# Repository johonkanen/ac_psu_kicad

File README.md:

# ac_psu_kicad

Migration of the **single_phase_inverter_psu_v3** board ("Inverter PSU") from Proteus 8.12
to KiCad 10. The KiCad schematic is redrawn from the Proteus PDF, and the PCB is rebuilt
from the Proteus gerbers, so that every pad, track, via and pour carries a net from the new
schematic. The goal is a KiCad design that is **electrically identical** to the Proteus
original.

The Proteus project file is binary and cannot be read, so the IPC-D-356A netlist in the
CADCAM export is the reference: 208 nets, 267 parts, 1075 pads, each with net, refdes, pin
and coordinates. Every check in this repo compares against that file.

- `PLAN.md`: the full plan, inventory of the source files, risks and model usage.
- `STATUS.md`: what is done, the last verification output, findings about the original
  design, and what comes next.
- `next_prompt.md`: the prompt for the next work session, replaced at the end of every
  phase.

## Board

<!-- board-plots:start -->
<!-- Generated by kicad-board-plots; edits between these markers are overwritten. -->

3D renders and copper layers of `kicad/ac_psu.kicad_pcb`, the layers in stack order without silkscreen. Plotted by [kicad-board-plots](https://github.com/johonkanen/kicad-board-plots) on each board change; the images live on the `renders` branch.

<table>
<tr>
<td align="center"><br><b>3D, top</b></td>
<td align="center"><br><b>3D, bottom (seen from below)</b></td>
</tr>
<tr>
<td align="center"><br><b>F.Cu: signal, FILTER_INPUT, DC+, DAB_CAP_PRI, 5V_ISOL, ISOPGND and 20 more pours (top)</b></td>
<td align="center"><br><b>In1.Cu: signal, DAB_SOURCE_HI_PRI, ISOGND, PGND, Q7_G, GND and 8 more pours</b></td>
</tr>
<tr>
<td align="center"><br><b>In2.Cu: signal, G3_SOURCE_HI, DAB_SOURCE_HI_SEC, PGND, Q7_S, DAB_GATE_HI_PRI and 8 more pours</b></td>
<td align="center"><br><b>B.Cu: signal, 15V_ISO, DAB_SOURCE_HI_SEC, SHUNT1_FORCE, ISODC+, INDUCTOR_OUTPUT and 12 more pours (bottom, seen from the top)</b></td>
</tr>
</table>

<!-- board-plots:end -->

## Layout

```
source/      Proteus exports (read-only): schematic PDF + page renders, CADCAM zip
             (gerbers, drill, IPC-D-356A netlist)
reference/   tables generated from the IPC netlist: pads (CSV/JSON), pin→net per part,
             pins per net
lib/         ac_psu.kicad_sym (project symbols, pin numbers = IPC pin ids),
             ac_psu.pretty (project footprints), part_map.csv (refdes → sheet, symbol,
             value), footprint_map.csv (refdes → footprint)
kicad/       KiCad project: root sheet + 11 hierarchical sheets, ac_psu.kicad_pcb
             (Proteus-generated up to tag proteus-conversion-complete, v4 edits by tools/v4/)
tools/       scripts and checks (see below)
reports/     generated reports: footprint fit, net assignment, pour nets (committed);
             ERC and DRC (not committed)
```

## Phases

| Phase | Content | State |
|---|---|---|
| 0 | Tooling: KiCad AppImage wrappers, IPC-D-356A parser, pin/net reference tables | done |
| 1 | Schematic: symbol library and part map, netlist comparison script, project skeleton, transcription of the 11 sheets from the PDF | done |
| 2 | Footprints for every symbol, pad numbers = IPC pin ids, checked by fitting footprint pads onto the IPC pad coordinates | done |
| 3 | PCB: place footprints at the Proteus positions, convert gerber tracks/vias/pours into KiCad tracks, vias and zones, assign nets by copper connectivity | done |
| 4 | Verification: schematic netlist ≡ IPC, DRC clean, gerber round-trip overlay, regenerated IPC-356 pad list diff | not started |

`STATUS.md` holds the current state; this table is only updated when a phase finishes.

## Requirements

- KiCad 10.0.7 AppImage at `~/kicad/kicad-10.0.7-x86_64.AppImage`. The scripts mount it
  on demand and use its `kicad-cli` and Python (with `pcbnew`). Do not run the AppImage
  with `--version`; it hangs.
- Python 3 for the plain scripts.

## Tools

The generic tools are the shared [proteus2kicad](https://github.com/johonkanen/proteus2kicad)
repository, a git submodule in `tools/p2k` (clone with `git clone --recurse-submodules`, or
run `git submodule update --init`). Board values (source files, refdes/net fix-ups, expected
counts, layers, outline) are in `p2k_config.py`. The scripts in `tools/` are the ones not
moved yet; they import the shared modules from `p2k`. Wrappers: `tools/p2k/bin/p2k <tool>`,
`tools/p2k/bin/kipy` (KiCad's Python with pcbnew), `tools/p2k/bin/kicad-cli`.
The generic migration method distilled from this board, the playbook, is in proteus2kicad
(`tools/p2k/CONVERSION_PLAYBOOK.md`).

## Checks

Run everything with one command:

```sh
tools/check_all.sh
```

It runs:

| Step | Script |
|---|---|
| KiCad environment (pcbnew 10.0.7 loads) | `tools/p2k/bin/kipy` |
| IPC parser self-check | `tools/p2k/bin/p2k ipc356 --check` |
| Gerber X2 flashes and drills vs IPC, outline | `tools/p2k/bin/p2k check_sources` |
| Symbol library is up to date with its generator | `tools/gen_symbols.py --check` |
| Symbol pin sets match the IPC pins for every refdes (+ v4 deviations) | `tools/check_symbols_v4.py` |
| ERC | `tools/erc.sh` (report in `reports/erc.rpt`) |
| Schematic netlist vs IPC netlist (+ v4 deviations, values) | `tools/compare_netlists_v4.py` |
| Footprint library and map are up to date | `tools/gen_footprints.py --check` |
| Footprint pads fit the IPC pads (≤ 0.05 mm) | `tools/check_footprints.py --pcbnew` |
| Board pads/holes/vias vs IPC (position and net) | `tools/check_board.py` |
| Copper connectivity after zone fill: 0 shorts, 0 opens, every item on its group's net | `tools/assign_nets.py --check` |
| DRC with schematic parity: 0 shorts, 0 unconnected | `tools/drc.py` (report in `reports/drc.json`) |
| Domain net classes / DRC rules match the schematic (IEC 61010-1 gaps P, I, C, E) | `tools/v4/domain_rules.py --check` |
| Insulation spacing between the domains on every layer | `tools/v4/domain_gaps.py` |
| IPC-D-356 export vs Proteus, gerber round trip | `tools/ipc356_diff.py`, `tools/gerber_roundtrip.py --check` |

`p2k compare_netlists` exports the KiCad netlist and compares nets as sets of
(refdes, pin), so net names do not have to match. It reports pins on the wrong net, merged
or split nets, N/C mismatches, missing or extra parts and pins, and progress per sheet.
Use `--sheet N` to check one sheet while drawing.

Other tools: `gen_symbols.py` builds `lib/ac_psu.kicad_sym` from KiCad standard symbols
and box symbols (helpers in `p2k.symgen`); `p2k.sch_builder` is a small library for writing schematic sheets from
Python; `p2k.sexpr` reads and writes KiCad s-expression files; `p2k make_skeleton` created
the project skeleton once; `tools/sheets/sheetNN.py` generate the 11 sheets.

**v5** (aux flyback, control-card isolation; V5_PLAN.md, CTRL_ISOLATION_PLAN.md): parts in
`tools/v5/v5_parts.py`, deviations in `lib/v5_deviations.csv` / `lib/v5_copper.csv` (kinds remove,
rename, and pending-layout areas where the checks list items as pending), board step
`tools/v5/v5_1_aux_ctrl.py`; the layout itself is done in the KiCad GUI.

**Since v4 the design board `kicad/ac_psu.kicad_pcb` is frozen**: it is edited directly by small
committed pcbnew scripts (`tools/v4/fix_*.py`, see STATUS.md "v4 design fixes"), and the Proteus
comparisons apply exactly the deviations listed in `lib/v4_deviations.csv` / `lib/v4_copper.csv`
(`tools/deviations.py`; wrappers `tools/compare_netlists_v4.py`, `tools/check_symbols_v4.py`).
`tools/make_pcb.sh` now rebuilds the *Proteus* board from the schematic at tag
`proteus-conversion-complete` into `build/proteus/` (regression check of the conversion tools,
`tools/regen_check.sh`). The Proteus board was built with `tools/make_pcb.sh`: `build_pcb.py` (footprints, nets, outline,
mounting holes), `gerber_to_tracks.py` (Proteus copper gerbers → tracks and vias, using
`p2k.gerber`), `assign_nets.py` (nets by copper connectivity, `p2k.geom2d`) and
`pours_to_zones.py` (Proteus pours → filled zones). The output is reproducible byte for byte.

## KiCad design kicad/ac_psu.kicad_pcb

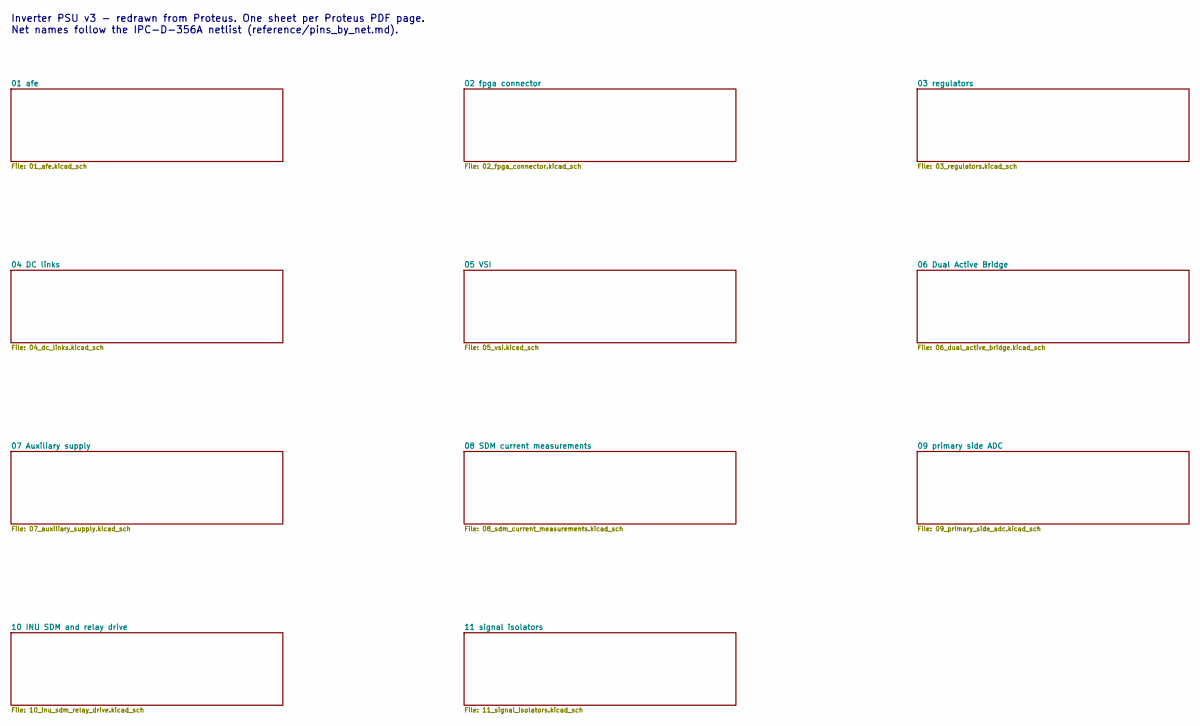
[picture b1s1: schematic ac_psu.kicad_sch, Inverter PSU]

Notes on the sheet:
Inverter PSU v3 - redrawn from Proteus. One sheet per Proteus PDF page. Net names follow the IPC-D-356A netlist (reference/pins_by_net.md).

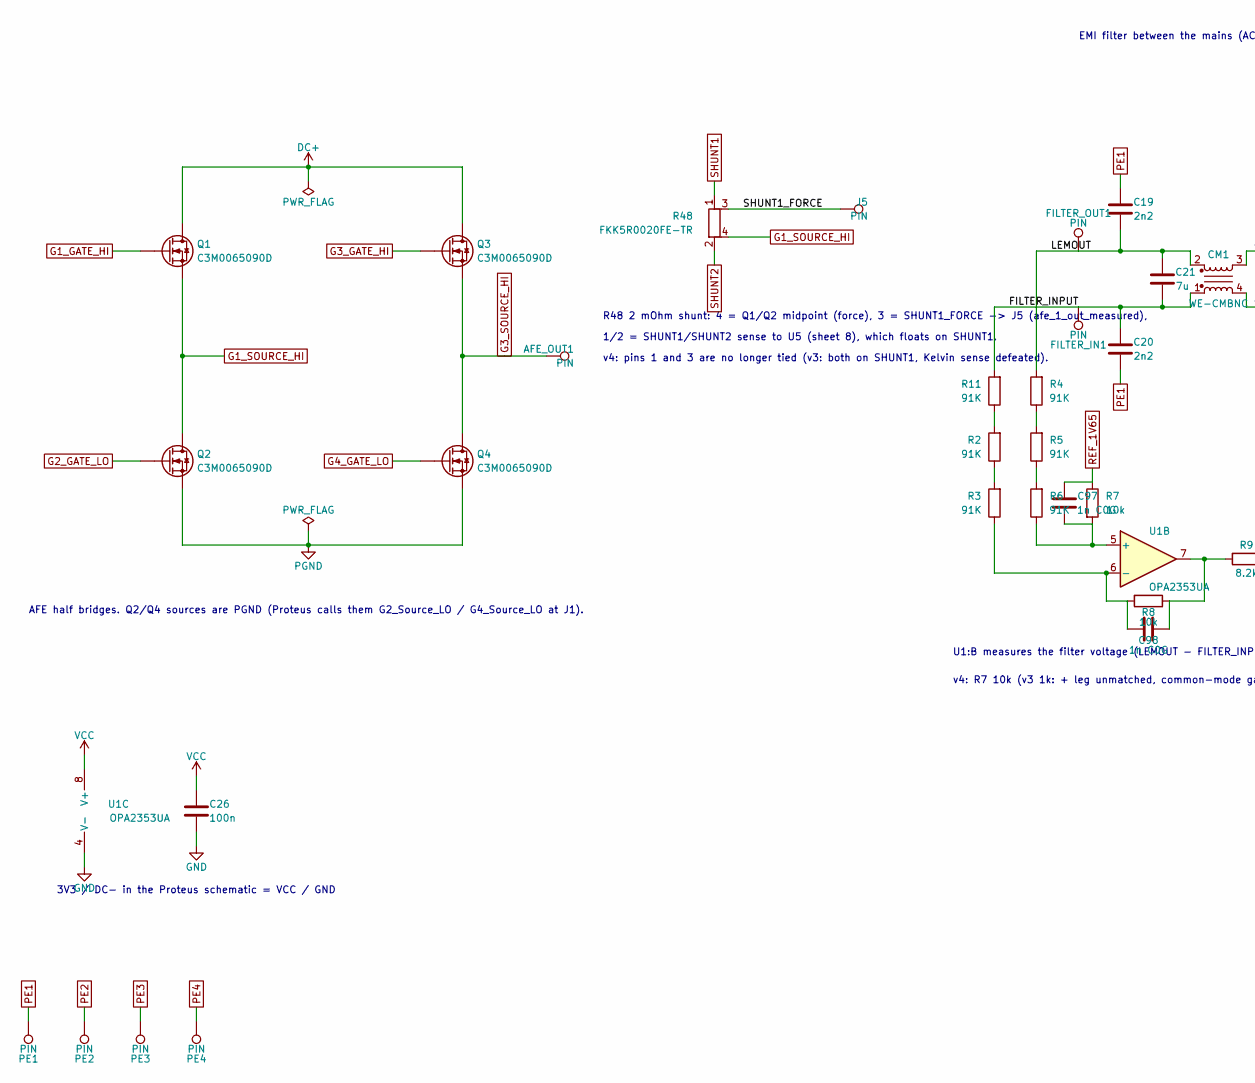
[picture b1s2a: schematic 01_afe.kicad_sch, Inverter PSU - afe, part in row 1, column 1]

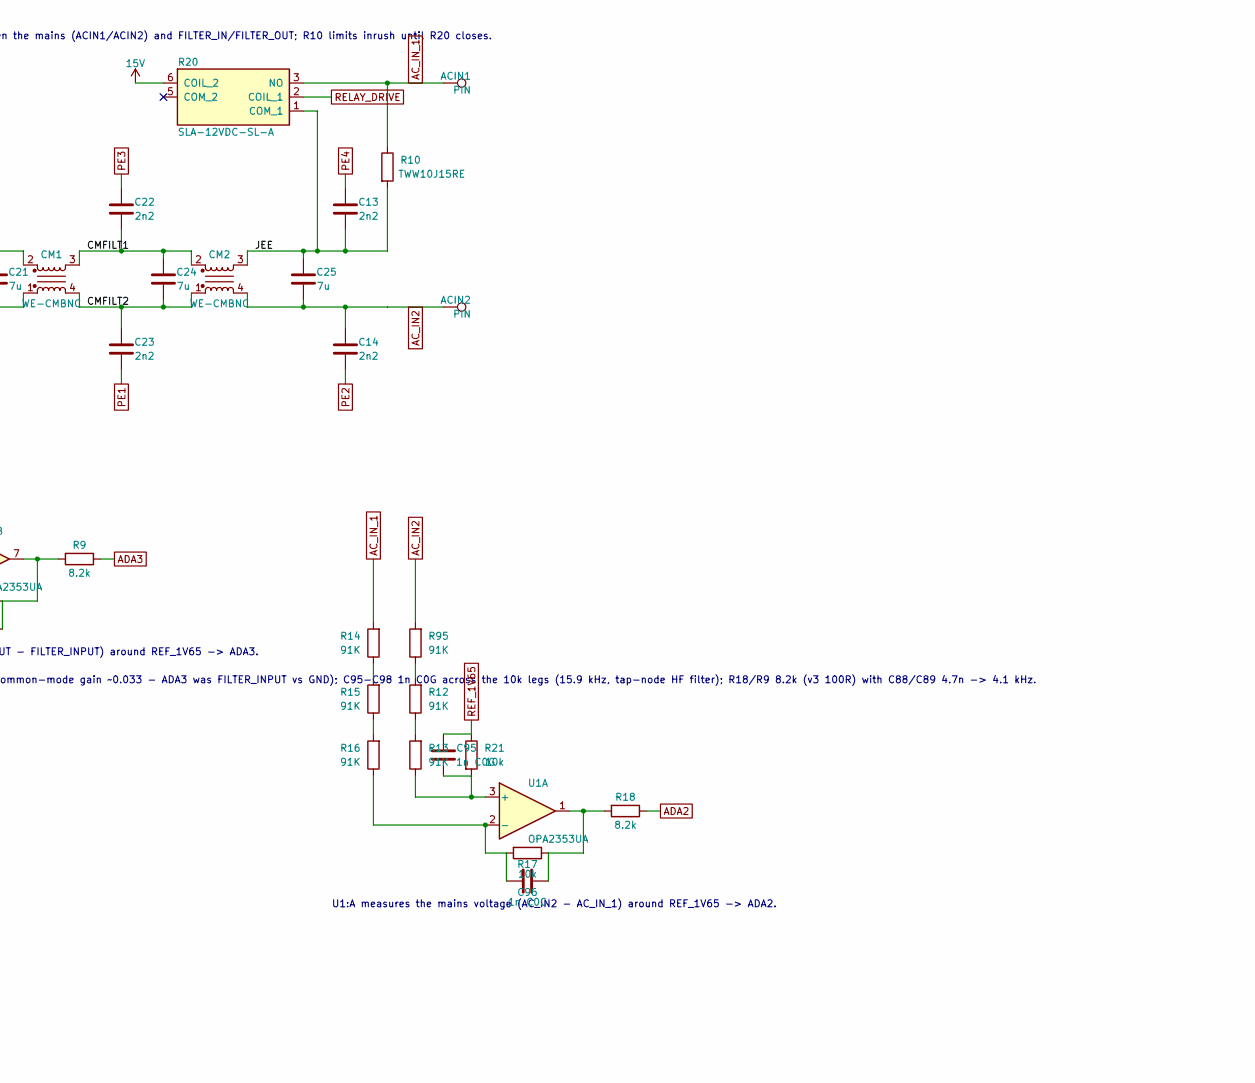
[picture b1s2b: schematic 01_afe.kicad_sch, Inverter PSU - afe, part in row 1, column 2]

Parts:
ACIN1, ACIN2: PIN; Terminal_2x1_P5.00mm_D2.0mm_Drill1.4mm
AFE_OUT1: PIN; Terminal_D4.0mm_Drill2.55mm
C13, C14, C19, C20, C22, C23: 2n2; C_Disc_D12.5mm_W5.0mm_P7.50mm
C21, C25: 7u; C_Rect_L33.0mm_W20.0mm_P27.50mm_MKS4_Proteus
C24: 7u; C_Rect_L33.0mm_W20.0mm_P27.50mm_MKS4
C26: 100n; C_0402_1005Metric
C95, C96, C97, C98: 1n C0G; C_0402_1005Metric
CM1, CM2: WE-CMBNC; L_CommonMode_WE-CMBNC
FILTER_IN1: PIN; Wuerth_REDCUBE-THR_74650074_M4_PTH
FILTER_OUT1: PIN; Wuerth_REDCUBE-THR_74650074_M4_PTH
J5: PIN; Wuerth_REDCUBE-THR_74650074_M4_PTH
PE1: PIN; Terminal_D4.0mm_Drill3.0mm
PE2, PE4: PIN; Terminal_D4.0mm_Drill2.0mm
PE3: PIN; Terminal_D4.0mm_Drill2.55mm
Q1, Q2, Q3, Q4: C3M0065090D; TO-247-3_Vertical_Proteus
R2, R3, R4, R5, R6, R11, R12, R13, R14, R15, R16, R95: 91K; R_1206_3216Metric_Pad1.30x1.75mm_HandSolder
R7, R8, R17, R21: 10k; R_0402_1005Metric
R9, R18: 8.2k; R_0402_1005Metric
R10: TWW10J15RE; R_Radial_Power_L13.0mm_W9.0mm_P5.00mm
R20: SLA-12VDC-SL-A; Relay_SLA-12VDC-SL-A
R48: FKK5R0020FE-TR; R_Shunt_FKK5R0020FE
U1: OPA2353UA; TSSOP-8_3x3mm_P0.65mm_Proteus

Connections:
15V: R20.6 (COIL_2); also elsewhere on the board
/01 afe/CMFILT1: C22.2, C24.1, CM1.3, CM2.2
/01 afe/CMFILT2: C23.2, C24.2, CM1.4, CM2.1
/01 afe/FILTER_INPUT: C20.2, C21.2, CM1.1, FILTER_IN1.1, R11.2
/01 afe/JEE: C13.2, C25.1, CM2.3, R10.2, R20.1 (COM_1)
/01 afe/LEMOUT: C19.2, C21.1, CM1.2, FILTER_OUT1.1, R4.2
/01 afe/SHUNT1_FORCE: J5.1, R48.3
AC_IN2: ACIN2.1, C14.2, C25.2, CM2.4, R95.2
AC_IN_1: ACIN1.1, R10.1, R14.2, R20.3 (NO)
ADA2: R18.1; also elsewhere on the board
ADA3: R9.1; also elsewhere on the board
DC+: Q1.2 (D), Q3.2 (D); also elsewhere on the board
G1_GATE_HI: Q1.1 (G); also elsewhere on the board
G1_SOURCE_HI: Q1.3 (S), Q2.2 (D), R48.4; also elsewhere on the board
G2_GATE_LO: Q2.1 (G); also elsewhere on the board
G3_GATE_HI: Q3.1 (G); also elsewhere on the board
G3_SOURCE_HI: AFE_OUT1.1, Q3.3 (S), Q4.2 (D); also elsewhere on the board
G4_GATE_LO: Q4.1 (G); also elsewhere on the board
GND: C26.1, U1.4 (V-); also elsewhere on the board
unnamed: C96.1, R17.1, R18.2, U1.1
unnamed: C98.1, R8.1, R9.2, U1.7
unnamed: R2.1, R3.2
unnamed: R4.1, R5.2
unnamed: R5.1, R6.2
unnamed: R2.2, R11.1
unnamed: R12.1, R13.2
unnamed: R12.2, R95.1
unnamed: R14.1, R15.2
unnamed: R15.1, R16.2
unnamed: C95.2, R13.1, R21.2, U1.3 (+)
unnamed: C96.2, R16.1, R17.2, U1.2 (-)
unnamed: C97.2, R6.1, R7.2, U1.5 (+)
unnamed: C98.2, R3.1, R8.2, U1.6 (-)
PE1: C19.1, C20.1, C23.1, PE1.1
PE2: C14.1, PE2.1
PE3: C22.1, PE3.1
PE4: C13.1, PE4.1
PGND: Q2.3 (S), Q4.3 (S); also elsewhere on the board
REF_1V65: C95.1, C97.1, R7.1, R21.1; also elsewhere on the board
RELAY_DRIVE: R20.2 (COIL_1); also elsewhere on the board
SHUNT1: R48.1; also elsewhere on the board
SHUNT2: R48.2; also elsewhere on the board
VCC: C26.2, U1.8 (V+); also elsewhere on the board

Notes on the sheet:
AFE half bridges. Q2/Q4 sources are PGND (Proteus calls them G2_Source_LO / G4_Source_LO at J1).
R48 2 mOhm shunt: 4 = Q1/Q2 midpoint (force), 3 = SHUNT1_FORCE -> J5 (afe_1_out_measured),
1/2 = SHUNT1/SHUNT2 sense to U5 (sheet 8), which floats on SHUNT1.
v4: pins 1 and 3 are no longer tied (v3: both on SHUNT1, Kelvin sense defeated).
EMI filter between the mains (ACIN1/ACIN2) and FILTER_IN/FILTER_OUT; R10 limits inrush until R20 closes.
U1:B measures the filter voltage (LEMOUT - FILTER_INPUT) around REF_1V65 -> ADA3.
v4: R7 10k (v3 1k: + leg unmatched, common-mode gain ~0.033 - ADA3 was FILTER_INPUT vs GND); C95-C98 1n C0G across the 10k legs (15.9 kHz, tap-node HF filter); R18/R9 8.2k (v3 100R) with C88/C89 4.7n -> 4.1 kHz.
U1:A measures the mains voltage (AC_IN2 - AC_IN_1) around REF_1V65 -> ADA2.
3V3 / DC- in the Proteus schematic = VCC / GND

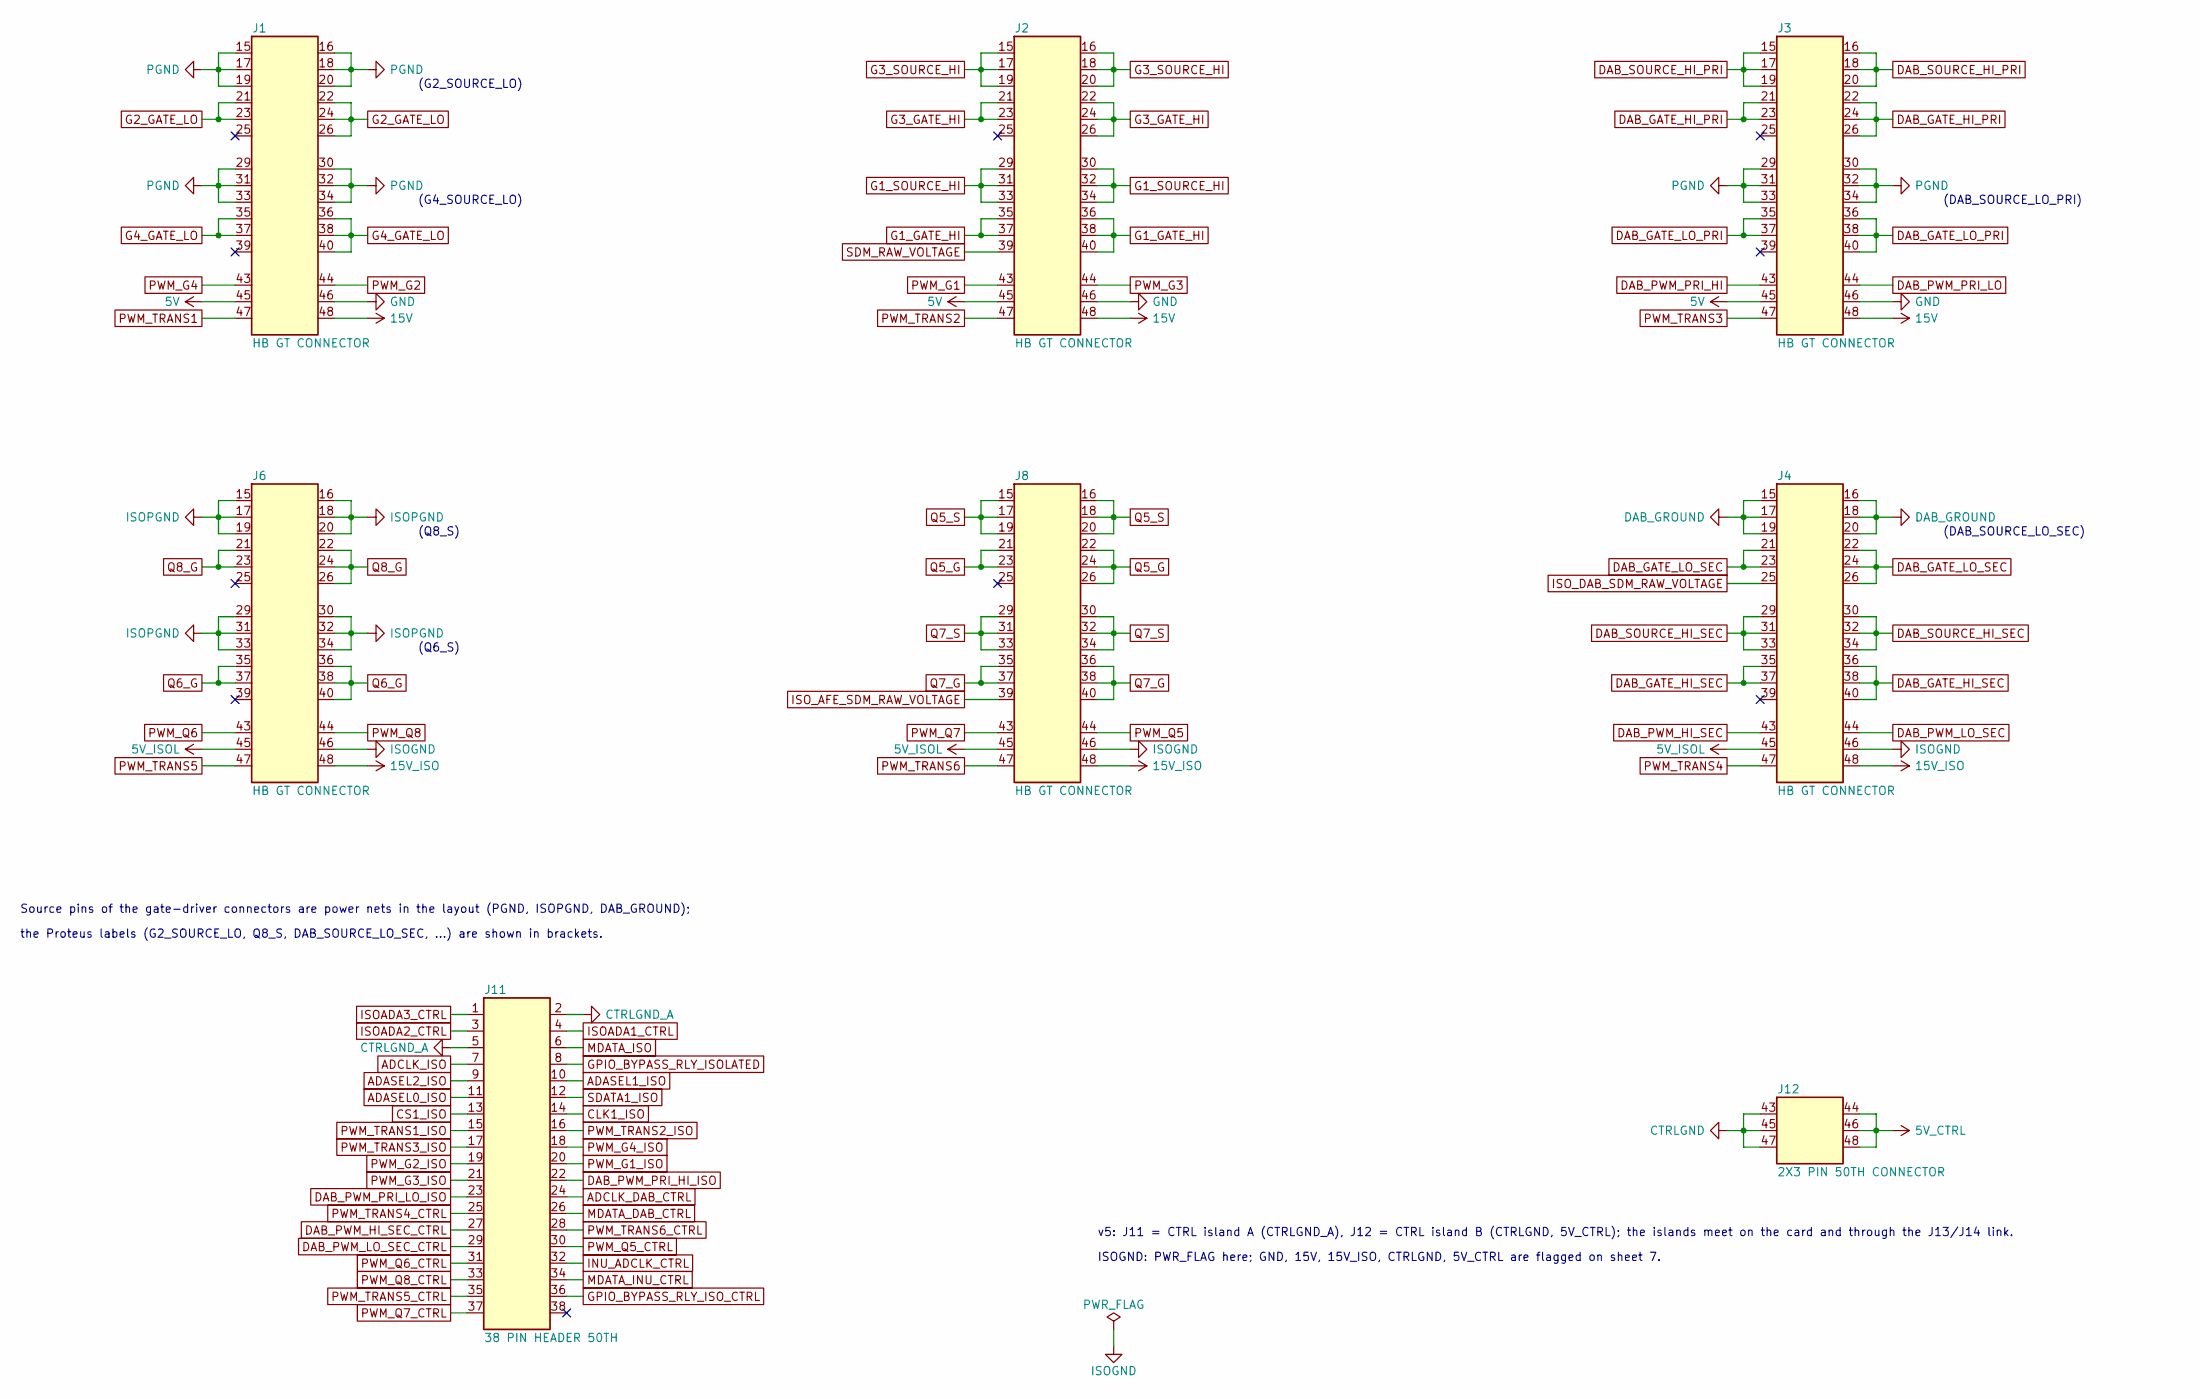
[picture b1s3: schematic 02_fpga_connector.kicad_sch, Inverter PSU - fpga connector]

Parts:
J1, J2, J3, J4, J6, J8: HB GT CONNECTOR; PinHeader_2x24_P1.27mm_Vertical_Pins15-48
J11: 38 PIN HEADER 50TH; PinHeader_2x19_P1.27mm_Vertical_Proteus
J12: 2X3 PIN 50TH CONNECTOR; PinHeader_2x03_P1.27mm_Vertical_Pins43-48

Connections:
5V: J1.45, J2.45, J3.45; also elsewhere on the board
5V_CTRL: J12.44, J12.46, J12.48; also elsewhere on the board
5V_ISOL: J4.45, J6.45, J8.45; also elsewhere on the board
15V: J1.48, J2.48, J3.48; also elsewhere on the board
15V_ISO: J4.48, J6.48, J8.48; also elsewhere on the board
ADASEL0_ISO: J11.11; also elsewhere on the board
ADASEL1_ISO: J11.10; also elsewhere on the board
ADASEL2_ISO: J11.9; also elsewhere on the board
ADCLK_DAB_CTRL: J11.24; also elsewhere on the board
ADCLK_ISO: J11.7; also elsewhere on the board
CLK1_ISO: J11.14; also elsewhere on the board
CS1_ISO: J11.13; also elsewhere on the board
CTRLGND: J12.43, J12.45, J12.47; also elsewhere on the board
CTRLGND_A: J11.2, J11.5; also elsewhere on the board
DAB_GATE_HI_PRI: J3.21, J3.22, J3.23, J3.24, J3.26; also elsewhere on the board
DAB_GATE_HI_SEC: J4.35, J4.36, J4.37, J4.38, J4.40; also elsewhere on the board
DAB_GATE_LO_PRI: J3.35, J3.36, J3.37, J3.38, J3.40; also elsewhere on the board
DAB_GATE_LO_SEC: J4.21, J4.22, J4.23, J4.24, J4.26; also elsewhere on the board
DAB_GROUND: J4.15, J4.16, J4.17, J4.18, J4.19, J4.20; also elsewhere on the board
DAB_PWM_HI_SEC: J4.43; also elsewhere on the board
DAB_PWM_HI_SEC_CTRL: J11.27; also elsewhere on the board
DAB_PWM_LO_SEC: J4.44; also elsewhere on the board
DAB_PWM_LO_SEC_CTRL: J11.29; also elsewhere on the board
DAB_PWM_PRI_HI: J3.43; also elsewhere on the board
DAB_PWM_PRI_HI_ISO: J11.22; also elsewhere on the board
DAB_PWM_PRI_LO: J3.44; also elsewhere on the board
DAB_PWM_PRI_LO_ISO: J11.23; also elsewhere on the board
DAB_SOURCE_HI_PRI: J3.15, J3.16, J3.17, J3.18, J3.19, J3.20; also elsewhere on the board
DAB_SOURCE_HI_SEC: J4.29, J4.30, J4.31, J4.32, J4.33, J4.34; also elsewhere on the board
G1_GATE_HI: J2.35, J2.36, J2.37, J2.38, J2.40; also elsewhere on the board
G1_SOURCE_HI: J2.29, J2.30, J2.31, J2.32, J2.33, J2.34; also elsewhere on the board
G2_GATE_LO: J1.21, J1.22, J1.23, J1.24, J1.26; also elsewhere on the board
G3_GATE_HI: J2.21, J2.22, J2.23, J2.24, J2.26; also elsewhere on the board
G3_SOURCE_HI: J2.15, J2.16, J2.17, J2.18, J2.19, J2.20; also elsewhere on the board
G4_GATE_LO: J1.35, J1.36, J1.37, J1.38, J1.40; also elsewhere on the board
GND: J1.46, J2.46, J3.46; also elsewhere on the board
GPIO_BYPASS_RLY_ISOLATED: J11.8; also elsewhere on the board
GPIO_BYPASS_RLY_ISO_CTRL: J11.36; also elsewhere on the board
INU_ADCLK_CTRL: J11.32; also elsewhere on the board
ISOADA1_CTRL: J11.4; also elsewhere on the board
ISOADA2_CTRL: J11.3; also elsewhere on the board
ISOADA3_CTRL: J11.1; also elsewhere on the board
ISOGND: J4.46, J6.46, J8.46; also elsewhere on the board
ISOPGND: J6.15, J6.16, J6.17, J6.18, J6.19, J6.20, J6.29, J6.30, J6.31, J6.32, J6.33, J6.34; also elsewhere on the board
ISO_AFE_SDM_RAW_VOLTAGE: J8.39; also elsewhere on the board
ISO_DAB_SDM_RAW_VOLTAGE: J4.25; also elsewhere on the board
MDATA_DAB_CTRL: J11.26; also elsewhere on the board
MDATA_INU_CTRL: J11.34; also elsewhere on the board
MDATA_ISO: J11.6; also elsewhere on the board
PGND: J1.15, J1.16, J1.17, J1.18, J1.19, J1.20, J1.29, J1.30, J1.31, J1.32, J1.33, J1.34, J3.29, J3.30, J3.31, J3.32, J3.33, J3.34; also elsewhere on the board
PWM_G1: J2.43; also elsewhere on the board
PWM_G1_ISO: J11.20; also elsewhere on the board
PWM_G2: J1.44; also elsewhere on the board
PWM_G2_ISO: J11.19; also elsewhere on the board
PWM_G3: J2.44; also elsewhere on the board
PWM_G3_ISO: J11.21; also elsewhere on the board
PWM_G4: J1.43; also elsewhere on the board
PWM_G4_ISO: J11.18; also elsewhere on the board
PWM_Q5: J8.44; also elsewhere on the board
PWM_Q5_CTRL: J11.30; also elsewhere on the board
PWM_Q6: J6.43; also elsewhere on the board
PWM_Q6_CTRL: J11.31; also elsewhere on the board
PWM_Q7: J8.43; also elsewhere on the board
PWM_Q7_CTRL: J11.37; also elsewhere on the board
PWM_Q8: J6.44; also elsewhere on the board
PWM_Q8_CTRL: J11.33; also elsewhere on the board
PWM_TRANS1: J1.47; also elsewhere on the board
PWM_TRANS1_ISO: J11.15; also elsewhere on the board
PWM_TRANS2: J2.47; also elsewhere on the board
PWM_TRANS2_ISO: J11.16; also elsewhere on the board
PWM_TRANS3: J3.47; also elsewhere on the board
PWM_TRANS3_ISO: J11.17; also elsewhere on the board
PWM_TRANS4: J4.47; also elsewhere on the board
PWM_TRANS4_CTRL: J11.25; also elsewhere on the board
PWM_TRANS5: J6.47; also elsewhere on the board
PWM_TRANS5_CTRL: J11.35; also elsewhere on the board
PWM_TRANS6: J8.47; also elsewhere on the board
PWM_TRANS6_CTRL: J11.28; also elsewhere on the board
Q5_G: J8.21, J8.22, J8.23, J8.24, J8.26; also elsewhere on the board
Q5_S: J8.15, J8.16, J8.17, J8.18, J8.19, J8.20; also elsewhere on the board
Q6_G: J6.35, J6.36, J6.37, J6.38, J6.40; also elsewhere on the board
Q7_G: J8.35, J8.36, J8.37, J8.38, J8.40; also elsewhere on the board
Q7_S: J8.29, J8.30, J8.31, J8.32, J8.33, J8.34; also elsewhere on the board
Q8_G: J6.21, J6.22, J6.23, J6.24, J6.26; also elsewhere on the board
SDATA1_ISO: J11.12; also elsewhere on the board
SDM_RAW_VOLTAGE: J2.39; also elsewhere on the board

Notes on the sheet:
(G2_SOURCE_LO)
(G4_SOURCE_LO)
(DAB_SOURCE_LO_PRI)
(Q8_S)
(Q6_S)
(DAB_SOURCE_LO_SEC)
Source pins of the gate-driver connectors are power nets in the layout (PGND, ISOPGND, DAB_GROUND);
the Proteus labels (G2_SOURCE_LO, Q8_S, DAB_SOURCE_LO_SEC, ...) are shown in brackets.
v5: J11 = CTRL island A (CTRLGND_A), J12 = CTRL island B (CTRLGND, 5V_CTRL); the islands meet on the card and through the J13/J14 link.
ISOGND: PWR_FLAG here; GND, 15V, 15V_ISO, CTRLGND, 5V_CTRL are flagged on sheet 7.

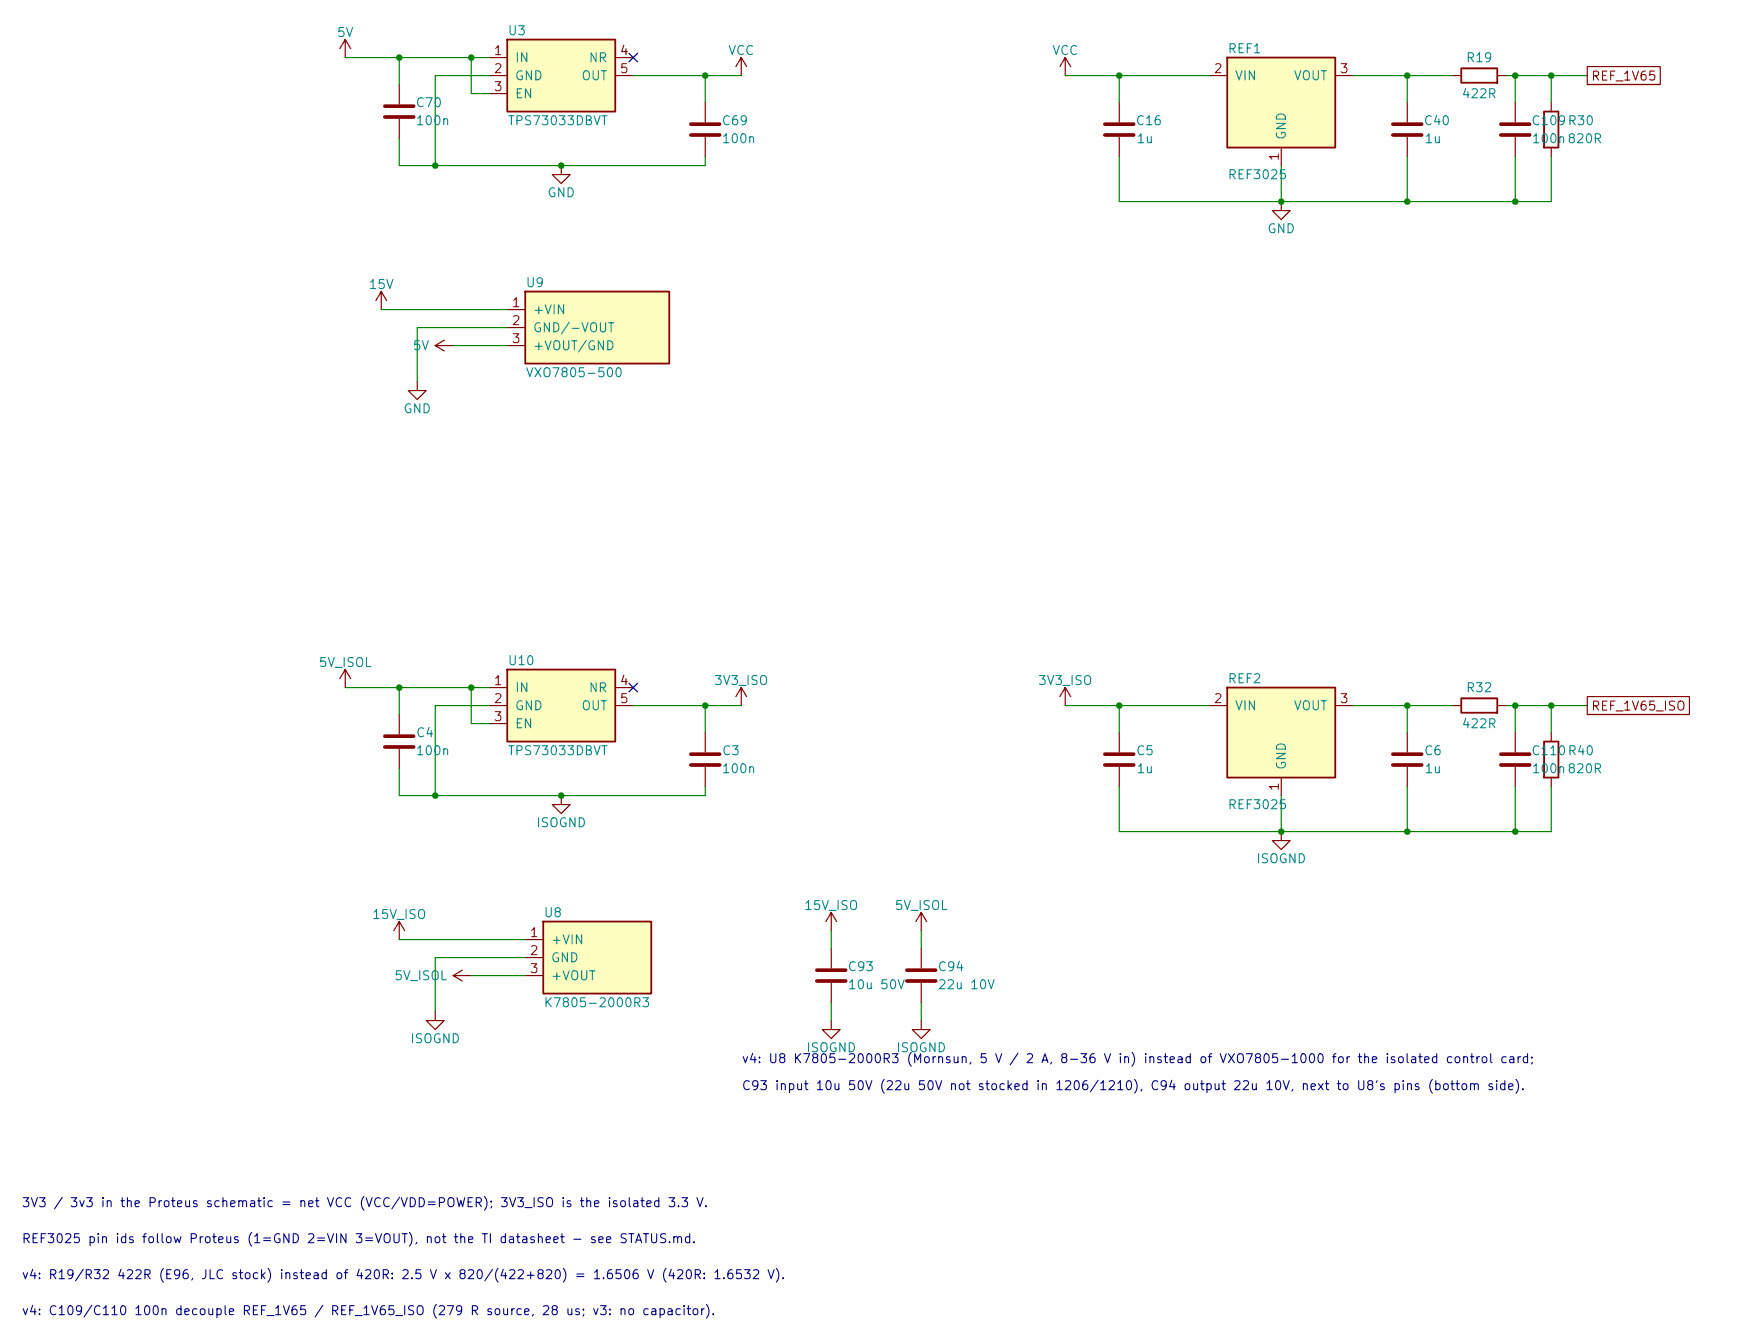
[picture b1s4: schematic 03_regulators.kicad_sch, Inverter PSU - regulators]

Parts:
C3, C4, C69, C70, C109, C110: 100n; C_0402_1005Metric
C5, C6, C16, C40: 1u; C_0402_1005Metric
C93: 10u 50V; C_1210_3225Metric
C94: 22u 10V; C_0805_2012Metric
R19, R32: 422R; R_0402_1005Metric
R30, R40: 820R; R_0402_1005Metric
REF1, REF2: REF3025; SOT-23_Proteus
U3, U10: TPS73033DBVT; SOT-23-5_TPS73033
U8: K7805-2000R3; Converter_DCDC_RECOM_R-78E-0.5_THT_Proteus
U9: VXO7805-500; Converter_DCDC_RECOM_R-78E-0.5_THT_Proteus

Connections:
3V3_ISO: C3.2, C5.2, REF2.2 (VIN), U10.5 (OUT); also elsewhere on the board
5V: C70.2, U3.1 (IN), U3.3 (EN), U9.3 (+VOUT/GND); also elsewhere on the board
5V_ISOL: C4.2, C94.1, U8.3 (+VOUT), U10.1 (IN), U10.3 (EN); also elsewhere on the board
15V: U9.1 (+VIN); also elsewhere on the board
15V_ISO: C93.1, U8.1 (+VIN); also elsewhere on the board
GND: C16.1, C40.1, C69.1, C70.1, C109.2, R30.2, REF1.1 (GND), U3.2 (GND), U9.2 (GND/-VOUT); also elsewhere on the board
ISOGND: C3.1, C4.1, C5.1, C6.1, C93.2, C94.2, C110.2, R40.2, REF2.1 (GND), U8.2 (GND), U10.2 (GND); also elsewhere on the board
unnamed: C40.2, R19.1, REF1.3 (VOUT)
unnamed: C6.2, R32.1, REF2.3 (VOUT)
REF_1V65: C109.1, R19.2, R30.1; also elsewhere on the board
REF_1V65_ISO: C110.1, R32.2, R40.1; also elsewhere on the board
VCC: C16.2, C69.2, REF1.2 (VIN), U3.5 (OUT); also elsewhere on the board

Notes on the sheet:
v4: U8 K7805-2000R3 (Mornsun, 5 V / 2 A, 8-36 V in) instead of VXO7805-1000 for the isolated control card;
C93 input 10u 50V (22u 50V not stocked in 1206/1210), C94 output 22u 10V, next to U8's pins (bottom side).
3V3 / 3v3 in the Proteus schematic = net VCC (VCC/VDD=POWER); 3V3_ISO is the isolated 3.3 V.
REF3025 pin ids follow Proteus (1=GND 2=VIN 3=VOUT), not the TI datasheet - see STATUS.md.
v4: R19/R32 422R (E96, JLC stock) instead of 420R: 2.5 V x 820/(422+820) = 1.6506 V (420R: 1.6532 V).
v4: C109/C110 100n decouple REF_1V65 / REF_1V65_ISO (279 R source, 28 us; v3: no capacitor).

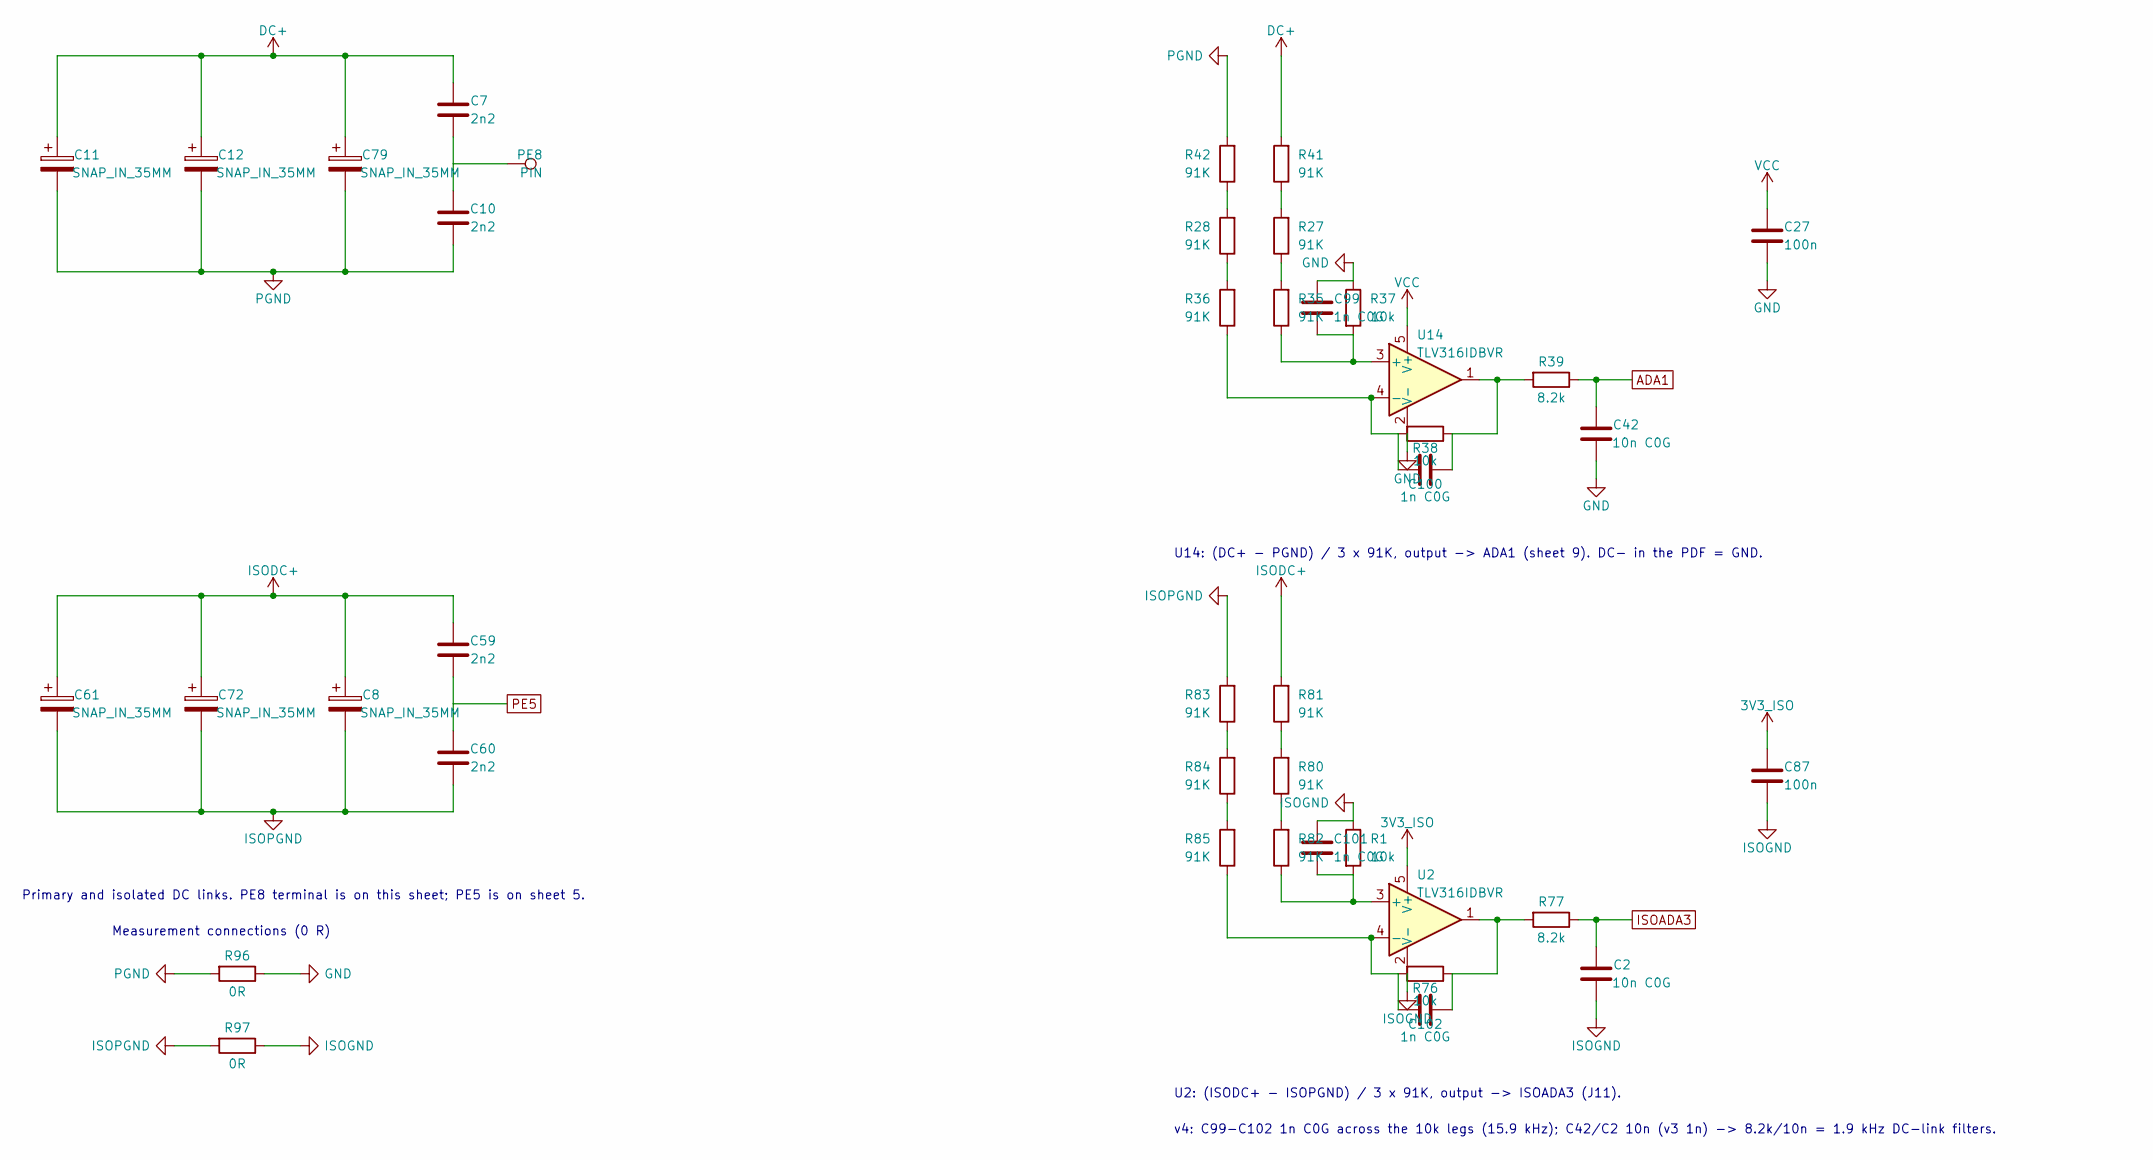
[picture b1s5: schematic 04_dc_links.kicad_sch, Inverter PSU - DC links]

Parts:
C2, C42: 10n C0G; C_0402_1005Metric
C7, C10, C59, C60: 2n2; C_Disc_D12.5mm_W5.0mm_P7.50mm
C8, C11, C12, C61, C72, C79: SNAP_IN_35MM; CP_Radial_D35.0mm_P10.00mm_SnapIn_Proteus
C27, C87: 100n; C_0402_1005Metric
C99, C100, C101, C102: 1n C0G; C_0402_1005Metric
PE8: PIN; Terminal_D3.05mm_Drill1.52mm
R1, R37, R38, R76: 10k; R_0402_1005Metric
R27, R28, R35, R36, R41, R42, R80, R81, R82, R83, R84, R85: 91K; R_1206_3216Metric_Pad1.30x1.75mm_HandSolder
R39, R77: 8.2k; R_0402_1005Metric
R96, R97: 0R; R_1206_3216Metric_Pad1.30x1.75mm_HandSolder
U2, U14: TLV316IDBVR; SOT-23-5_TLV316

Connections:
3V3_ISO: C87.2, U2.5 (V+); also elsewhere on the board
ADA1: C42.1, R39.1; also elsewhere on the board
DC+: C7.2, C11.1, C12.1, C79.1, R41.2; also elsewhere on the board
GND: C27.1, C42.2, C99.1, R37.1, R96.1, U14.2 (V-); also elsewhere on the board
ISOADA3: C2.1, R77.1; also elsewhere on the board
ISODC+: C8.1, C59.2, C61.1, C72.1, R81.2; also elsewhere on the board
ISOGND: C2.2, C87.1, C101.1, R1.1, R97.1, U2.2 (V-); also elsewhere on the board
ISOPGND: C8.2, C60.1, C61.2, C72.2, R83.2, R97.2; also elsewhere on the board
unnamed: C7.1, C10.2, PE8.1
unnamed: C100.1, R38.1, R39.2, U14.1
unnamed: C102.1, R76.1, R77.2, U2.1
unnamed: R27.1, R35.2
unnamed: R27.2, R41.1
unnamed: R28.1, R36.2
unnamed: R28.2, R42.1
unnamed: R80.1, R82.2
unnamed: R80.2, R81.1
unnamed: R83.1, R84.2
unnamed: R84.1, R85.2
unnamed: C101.2, R1.2, R82.1, U2.3 (+)
unnamed: C102.2, R76.2, R85.1, U2.4 (-)
unnamed: C99.2, R35.1, R37.2, U14.3 (+)
unnamed: C100.2, R36.1, R38.2, U14.4 (-)
PE5: C59.1, C60.2; also elsewhere on the board
PGND: C10.1, C11.2, C12.2, C79.2, R42.2, R96.2; also elsewhere on the board
VCC: C27.2, U14.5 (V+); also elsewhere on the board

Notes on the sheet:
Primary and isolated DC links. PE8 terminal is on this sheet; PE5 is on sheet 5.
Measurement connections (0 R)
U14: (DC+ - PGND) / 3 x 91K, output -> ADA1 (sheet 9). DC- in the PDF = GND.
U2: (ISODC+ - ISOPGND) / 3 x 91K, output -> ISOADA3 (J11).
v4: C99-C102 1n C0G across the 10k legs (15.9 kHz); C42/C2 10n (v3 1n) -> 8.2k/10n = 1.9 kHz DC-link filters.
